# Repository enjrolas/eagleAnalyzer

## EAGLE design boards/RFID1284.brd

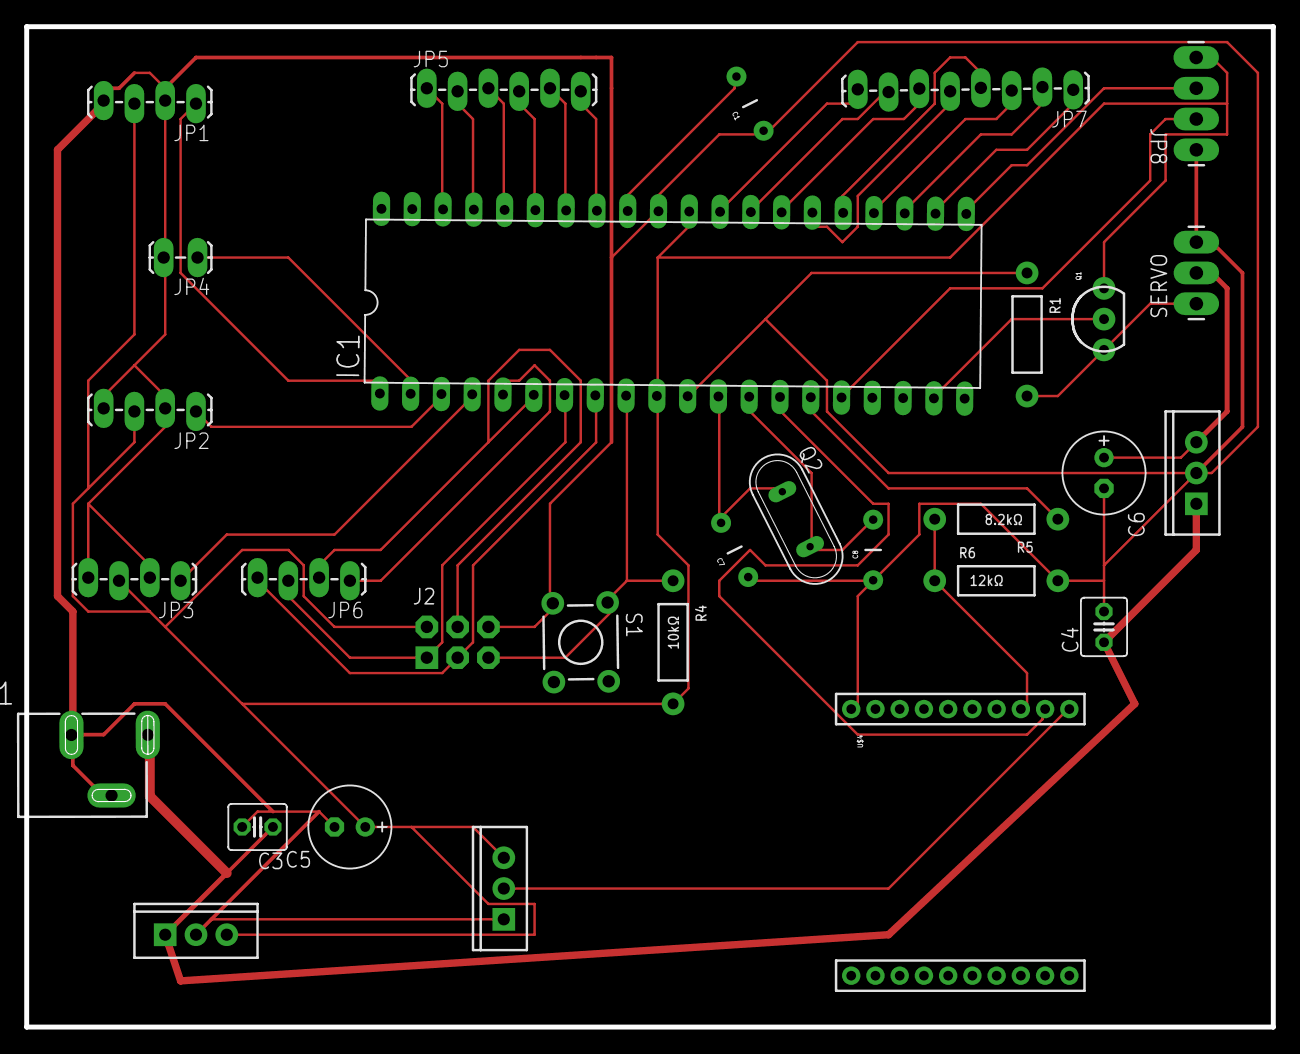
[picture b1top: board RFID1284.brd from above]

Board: 2 copper layers, 102.9 x 82.5 mm, 30 parts (0 on the bottom side), 38 nets.

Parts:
C1: 100nF; CAP-PTH-5MM
C3, C4: C025-040X050
C5, C6: E2,5-7
C7, C8: 20pF; CAP-PTH-5MM
IC1: DIL40
IC2, IC3, IC4: TO220-IGO
J1: POWER_JACKSLT; POWER_JACK_SLOT
J2: AVR_SPI_PRG_6NS; 2X3-NS
JP1, JP2, JP3, JP6: 1X04_LOCK_LONGPADS
JP4: 1X02_LOCK_LONGPADS
JP5: 1X06_LOCK_LONGPADS
JP7: 1X08_LOCK_LONGPADS
JP8: 1X04_LONGPADS
Q1: TO-92-AMMO
Q2: 16MHz; QS
R1: AXIAL-0.4
R4: 10kΩ; AXIAL-0.4
R5: 8.2kΩ; AXIAL-0.4
R6: 12kΩ; AXIAL-0.4
S1: TACTILE-PTH
SERVO: 1X03_LONGPADS
U$4: XBEE-1B1; XBEE-1

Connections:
5V: C5.+, IC1.10, IC1.30, IC2.OUT, IC4.OUT, J2.2, JP1.3, JP2.3, JP3.3, JP8.4, Q1.3, R4.P$2
DOOR_SWITCH: IC1.2, JP4.1
GND: C1.1, C3.2, C4.2, C5.-, C6.-, C7.1, C8.1, IC1.11, IC1.31, IC2.GND, IC3.GND, IC4.IN, J1.GND@1, J1.GND@2, J2.6, JP1.2, JP1.4, JP2.2, JP2.4, JP3.2, JP3.4, JP4.2, JP8.1, R1.P$1, R6.P$2, S1.3, SERVO.3, U$4.10
LOCK: IC1.3, JP2.1
LOCK_DELAY: IC1.4, JP3.1
MISO: IC1.7, J2.1, JP6.3
MOSI: IC1.6, J2.4, JP6.2
unnamed: C7.2, IC1.12, Q2.1
unnamed: C1.2, IC1.32
unnamed: C8.2, IC1.13, Q2.2
unnamed: IC1.38, JP5.1
unnamed: IC1.37, JP5.2
unnamed: IC1.36, JP5.3
unnamed: IC1.35, JP5.4
unnamed: IC1.34, JP5.5
unnamed: IC1.33, JP5.6
unnamed: IC1.22, JP7.1
unnamed: IC1.23, JP7.2
unnamed: IC1.24, JP7.3
unnamed: IC1.25, JP7.4
unnamed: IC1.26, JP7.5
unnamed: IC1.27, JP7.6
unnamed: IC1.28, JP7.7
unnamed: IC1.29, JP7.8
RESET: IC1.9, J2.5, R4.P$1, S1.1
RFID_ENABLE: IC1.21, JP8.3
RFID_SERIAL: IC1.16, JP8.2
SCK: IC1.8, J2.3, JP6.4
SERVO: IC1.19, Q1.2
SERVO_OUT: Q1.1, R1.P$2, SERVO.1
SERVO_VCC: C6.+, IC3.OUT, SERVO.2
SS: IC1.5, JP6.1
TX0: IC1.15, R5.P$1
TX0_LOW: R5.P$2, R6.P$1, U$4.3
UNLOCK: IC1.1, JP1.1
VCC: IC4.GND, U$4.1
VIN: C3.1, C4.1, IC2.IN, IC3.IN, J1.PWR
XBEE_OUT: IC1.14, U$4.2

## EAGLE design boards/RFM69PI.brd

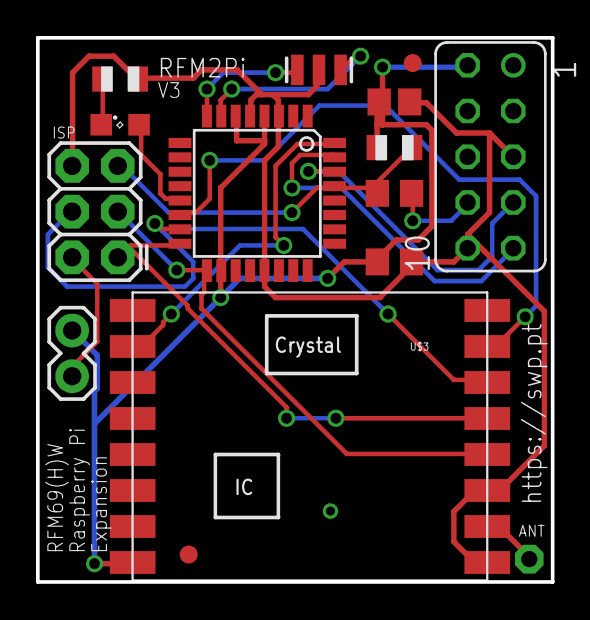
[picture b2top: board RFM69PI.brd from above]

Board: 2 copper layers, 28.6 x 30.2 mm, 15 parts (0 on the bottom side), 17 nets.

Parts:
ANT: 1,6/0,8
C4, C5, C7: 0.1uF; C0805
ISP: AVR_SPI_PRG_6PTH; 2X3
JP1: 1X02
LED1: SML0805
R1: 10K; R0805
RASPBERRY_PI: FE05-2
RLED: 220R; R0805
U2: ATMEGA168; TQFP32-08
U$1, U$2: FIDUCIAL; FIDUCIAL_1MM
U$3: RFM69; RFM69SMD
Y1: 16MHz; RESONATOR-SMD

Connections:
+3V3: C4.1, C7.1, JP1.2, R1.2, RASPBERRY_PI.2, U2.4, U2.6, U2.18, U$3.8
+5V: ISP.2, JP1.1
ANT: ANT.1, U$3.10
D0/RX: RASPBERRY_PI.7, U2.30
D1/TX: RASPBERRY_PI.9, U2.31
D2: U2.32, U$3.2
D9: LED1.A, U2.13
D10: U2.14, U$3.15
D11/MOSI: ISP.4, U2.15, U$3.14
D12/MISO: ISP.1, U2.16, U$3.13
D13/SCK: ISP.3, U2.17, U$3.12
GND: C4.2, C7.2, ISP.6, RASPBERRY_PI.5, RASPBERRY_PI.10, RLED.1, U2.3, U2.5, U2.21, U$3.9, U$3.11, Y1.2
unnamed: U2.7, Y1.1
unnamed: U2.8, Y1.3
unnamed: LED1.C, RLED.2
RESET: C5.2, ISP.5, R1.1, U2.29
_RESET: C5.1, RASPBERRY_PI.8

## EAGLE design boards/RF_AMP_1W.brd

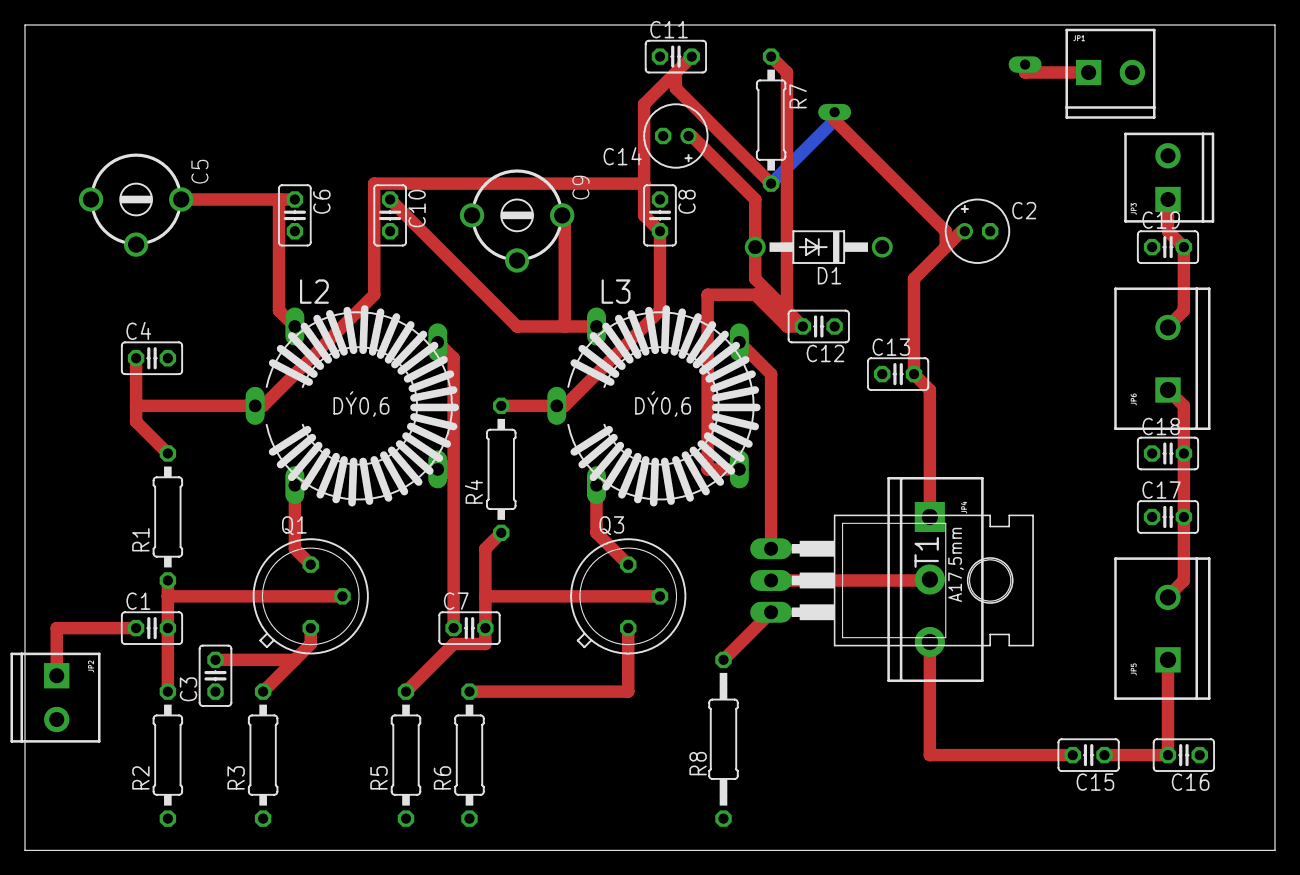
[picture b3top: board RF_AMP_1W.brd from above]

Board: 2 copper layers, 100.0 x 66.0 mm, 40 parts (1 on the bottom side), 21 nets.

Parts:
C1: C025-025X050
C2: 100uF; E2-5
C3, C7: 47nF; C025-025X050
C4, C8, C11, C12, C13, C15: 100nF; C025-025X050
C5, C9: CTRIM808-BC
C6, C10: 100pF; C025-025X050
C14: 10uF; E2-5
C16, C17, C18, C19: 560pF; C025-025X050
D1: 1N4004; DO41-10
JP1: SCREWTERMINAL-3.5MM-2
JP2: IN; SCREWTERMINAL-3.5MM-2
JP3: OUT; SCREWTERMINAL-3.5MM-2
JP4: SCREWTERMINAL-5MM-3
JP5: L7; SCREWTERMINAL-5MM-2
JP6: L8; SCREWTERMINAL-5MM-2
L1: JAF1 5uH VK200; 82114A
L2, L3: ED16
Q1, Q3: BFY50; TO39
R1, R4: 12K; 0207/10
R2, R5: 1.5K; 0207/10
R3: 100; 0207/10
R6: 33; 0207/10
R7: 1k; 0207/10
R8: 0207/12
T1: BUX85; TO220

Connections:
GND: C2.-, C3.1, C4.2, C5.2, C6.2, C8.1, C9.2, C10.2, C11.1, C12.1, C13.1, C14.-, C16.1, C17.1, C18.1, C19.1, D1.C, JP1.2, JP2.2, JP3.2, L2.OUT2, R2.1, R3.1, R5.1, R6.1, R8.1
unnamed: JP1.1, L1.1
unnamed: C2.+, C4.1, C8.2, C11.2, C13.2, JP4.1, L1.2, L2.A, L3.A, R1.2, R4.2, R7.2
unnamed: C1.2, Q1.2, R1.1, R2.2
unnamed: C1.1, JP2.1
unnamed: C3.2, Q1.1, R3.2
unnamed: L2.B, Q1.3
unnamed: C5.1, C6.1, L2.C
unnamed: R8.2, T1.3
unnamed: JP4.2, T1.2
unnamed: C7.2, Q3.2, R4.1, R5.2
unnamed: C15.2, JP4.3
unnamed: C15.1, C16.2, JP5.1
unnamed: Q3.1, R6.2
unnamed: L3.B, Q3.3
unnamed: C9.1, C10.1, L3.C
unnamed: L3.OUT1, T1.1
unnamed: C12.2, C14.+, D1.A, L3.OUT2, R7.1
unnamed: C7.1, L2.OUT1
unnamed: C17.2, C18.2, JP5.2, JP6.1
unnamed: C19.2, JP3.1, JP6.2

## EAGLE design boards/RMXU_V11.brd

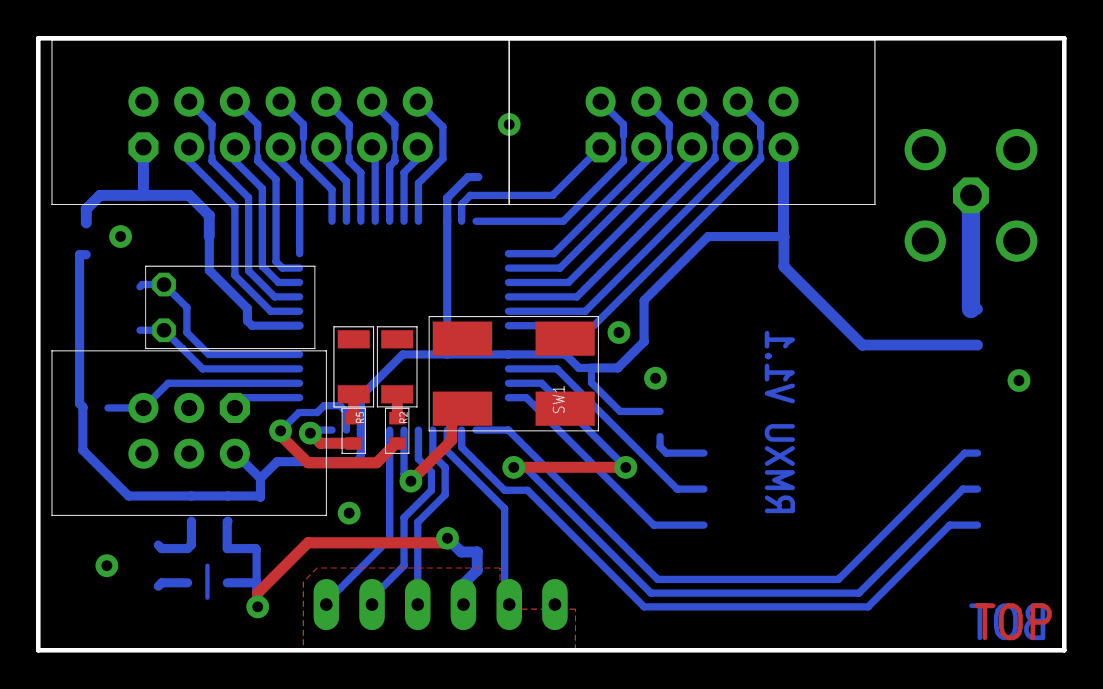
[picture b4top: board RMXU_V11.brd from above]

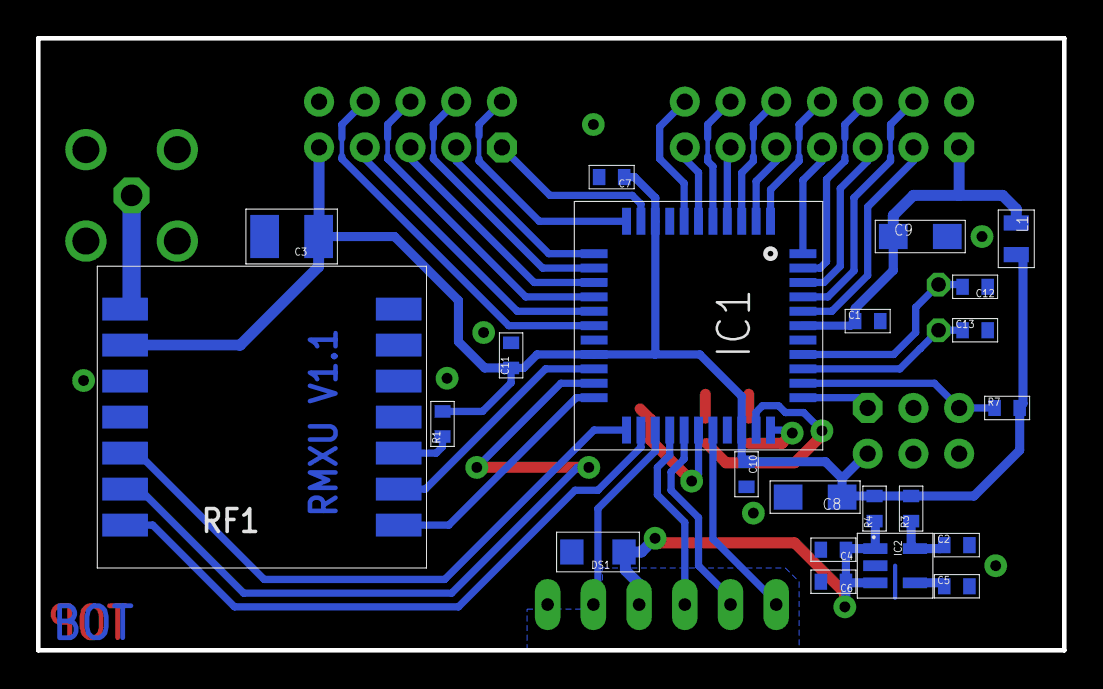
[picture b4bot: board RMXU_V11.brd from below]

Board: 2 copper layers, 57.0 x 34.0 mm, 42 parts (22 on the bottom side), 46 nets.

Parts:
C1, C6, C7, C10, C11: 100n; 0603
C2, C4: 1u; 0603
C3: 68u; SMC_B
C5: 10n; 0603
C8, C9: 10u; SMC_A
C12, C13: n.b.; 0603
DS1: SMF12A; SMF
IC1: XMEGA32A4U; TQFP44
IC2: LP2992IM5-3v3; SOT23-5
L1: 10uH; 0805
LED1: LEDG; 1206
LED3: LEDR; 1206
QR1: 32,768; TC26H
R1, R7: 10k; 0603
R2, R5: 1k; 0603
R3: 0R; 0603
R4: n.b.; 0603
RF1: RFM12B
SV1: PDI; ML6
SV2: PORTC; ML10
SV4: PORT A-B; ML14
SW1: SW1; SPNO
X2: ANT; T2.0/1.2
X3, X4, X5, X6: GND; T2.3/1.5
X7: DTR; T1.4/0.7L
X8: TX; T1.4/0.7L
X9: RX; T1.4/0.7L
X10: VCC; T1.4/0.7L
X11: CTS; T1.4/0.7L
X12: GND; T1.4/0.7L

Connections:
+3V3: C3.+, C7.1, C8.+, C10.1, C11.1, IC1.9, IC1.19, IC1.31, L1.2, R1.2, R3.2, R4.2, R7.2, RF1.VDD, SV1.2, SV2.9
CTS: IC1.25, X11.1
DTR: IC1.32, R2.2
GND: C1.2, C2.2, C3.-, C4.2, C5.2, C6.2, C7.2, C8.-, C9.-, C10.2, C11.2, C12.1, C13.2, DS1.A, IC1.8, IC1.18, IC1.30, IC1.38, IC2.2, LED1.2, LED3.2, RF1.GND, RF1.GND@1, SV1.6, SV2.10, SV4.2, SW1.1, SW1.2, X3.P$1, X4.P$1, X5.P$1, X6.P$1, X12.1
unnamed: IC1.10, SV2.1
unnamed: IC1.11, SV2.2
unnamed: IC1.12, SV2.3
unnamed: IC1.29, X7.1
unnamed: C12.2, IC1.37, QR1.1
unnamed: IC1.13, SV2.4
unnamed: IC1.14, SV2.5
unnamed: IC1.15, SV2.6
unnamed: IC1.16, SV2.7
unnamed: IC1.17, SV2.8
unnamed: RF1.ANT, X2.P$1
unnamed: IC1.33, R5.2
unnamed: C5.1, IC2.4
unnamed: IC1.28, SW1.3
unnamed: LED1.1, R2.1
unnamed: C13.1, IC1.36, QR1.2
unnamed: C2.1, IC2.5, R3.1
unnamed: R1.1, RF1.FFS
unnamed: LED3.1, R5.1
unnamed: C1.1, C9.+, IC1.39, L1.1, SV4.1
unnamed: IC1.7, SV4.14
unnamed: IC1.6, SV4.13
unnamed: IC1.5, SV4.12
unnamed: IC1.4, SV4.11
unnamed: IC1.3, SV4.10
unnamed: IC1.2, SV4.9
unnamed: IC1.1, SV4.8
unnamed: IC1.44, SV4.7
unnamed: IC1.43, SV4.6
unnamed: IC1.42, SV4.5
unnamed: IC1.41, SV4.4
unnamed: IC1.40, SV4.3
unnamed: IC1.34, SV1.1
unnamed: IC1.35, R7.1, SV1.5
RIRQ: IC1.20, RF1.IRQ
RSEL: IC1.24, RF1.SEL
RX: IC1.26, X9.1
RXDD0: IC1.22, RF1.SDO
TX: IC1.27, X8.1
TXDD0: IC1.23, RF1.SDI
VCC: C4.1, C6.1, DS1.C, IC2.1, IC2.3, R4.1, X10.1
XCKD0: IC1.21, RF1.SCK

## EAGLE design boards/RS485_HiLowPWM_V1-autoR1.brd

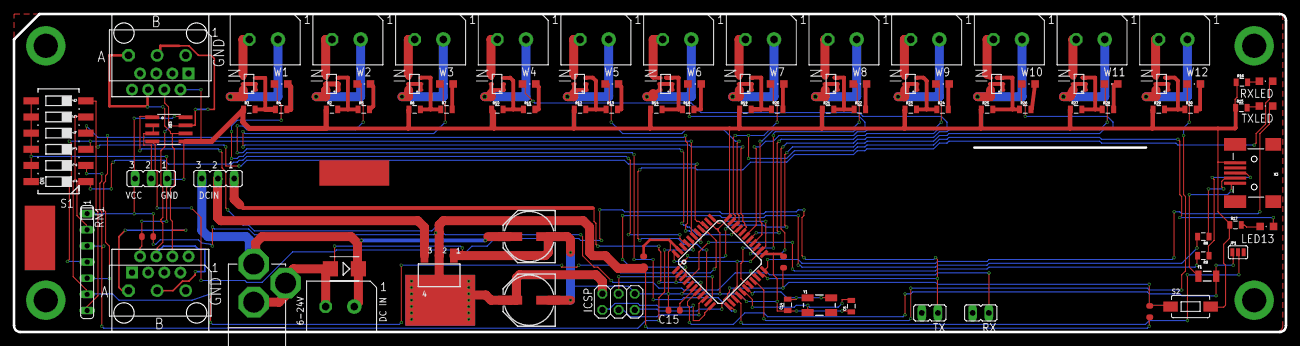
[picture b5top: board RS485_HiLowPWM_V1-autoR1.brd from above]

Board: 2 copper layers, 200.0 x 50.0 mm, 105 parts (0 on the bottom side), 94 nets.

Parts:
C3, C6, C7, C15: 100n; C0603-ROUND
C5, C14: 22p; 0805
C8: 47u; PANASONIC_E
C11: 100uF; PANASONIC_E
D1: M7; SMB
F1: PTCSMD; PTC-1206
IC1: ATMEGA32U4-AU; TQFP44
IC4: MC33269ST-5; SOT223
ICSP: ICSP; 2X03
JP1: PW_SW; SJ_3
JP3: PW_SOURCE; JP2
JP4: RS485_PW; JP2
JP10, JP11, JP12, JP13: M01-SMTSO-256-ET; SMTSO-256-ET
LED13: CHIPLED_0805
OUT1, OUT2: RJ45-8PTH; RJ45-8
R1: 10k; R0603-ROUND
R2, R3, R6, R10, R12, R14, R19, R21, R23, R25, R27, R29: 10K; 0805
R4, R5, R7, R11, R13, R18, R20, R22, R24, R26, R28, R30: 1K; 0805
R8, R9: 22; 0805
R15, R16, R17: 330; 0805
RN1: 1K; SIL7
RX: RX_TXO; JP1
RXLED: CHIPLED_0805
S1: 219-06; CTS-219-06
S2: RES; TACTILE-SWITCH-1101NE
TX: TX_RXI; JP1
TXLED: CHIPLED_0805
U$1, U$4, U$6, U$8, U$12, U$14, U$16, U$18, U$20, U$22, U$24, U$26: DECADE-NSS30201MR6T1G
U$2, U$5, U$7, U$9, U$11, U$13, U$15, U$17, U$19, U$21, U$23, U$25, U$27: DECADE-5MM-CONN; DECADE-5MM-CON-1X2
U$3: RS485SOIC; SO08
U$10: DECADE-LOGO-SMALL
U$28, U$29: DECADE-5MM-CON-1X3
U$30: LL-LUXURYLOGICO.COM; DECADE-LL-LOGO-SMALL
W1, W2, W3, W4, W5, W6, W7, W8, W9, W10, W11, W12: CHIPLED_0805
X1: DC21MMX; DC-21MM
X3: USBOLD; USB-MINIB-OLD
Y1: 16Mhz; CRYSTAL-SMD-5X3

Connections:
+5V: C6.1, C7.1, C8.+, IC4.2, IC4.4, ICSP.2, JP4.3, R1.2, RN1.1, U$3.8
A: OUT1.6, OUT2.6, U$3.6, U$28.3, U$29.3
B: OUT1.4, OUT2.4, U$3.7, U$28.2, U$29.2
D4: IC1.25, W11.A
D5: IC1.31, W5.A
D6: IC1.27, W4.A
D7: IC1.1, W10.A
D8: IC1.28, W9.A
D9: IC1.29, W3.A
D10: IC1.30, W2.A
D11: IC1.12, W1.A
D12: IC1.26, W8.A
D13: IC1.32, LED13.A, W7.A
GND: C3.2, C5.1, C6.2, C7.2, C8.-, C11.-, C14.1, C15.2, D1.A, IC1.5, IC1.15, IC1.23, IC1.33, IC1.35, IC1.43, IC4.1, ICSP.6, JP4.1, OUT1.2, OUT2.2, R2.1, R3.1, R6.1, R10.1, R12.1, R14.1, R15.1, R16.1, R17.1, R19.1, R21.1, R23.1, R25.1, R27.1, R29.1, S1.7, S1.8, S1.9, S1.10, S1.11, S1.12, S2.P$2, U$3.5, U$9.2, U$28.1, U$29.1, X1.1, X1.3, X3.GND
MISO: IC1.11, ICSP.1
MOSI: IC1.10, ICSP.4
unnamed: U$1.1, U$1.2, U$1.5, U$1.6, U$2.1
unnamed: R4.2, W1.C
unnamed: U$1.E, U$2.2
unnamed: R5.2, W2.C
unnamed: R3.2, R4.1, U$1.B
unnamed: C5.2, IC1.16, Y1.1
unnamed: C14.2, IC1.17, Y1.3
unnamed: R2.2, R5.1, U$4.B
unnamed: U$4.1, U$4.2, U$4.5, U$4.6, U$5.1
unnamed: U$4.E, U$5.2
unnamed: IC1.3, R8.2
unnamed: IC1.4, R9.2
unnamed: R8.1, X3.D-
unnamed: R9.1, X3.D+
unnamed: F1.1, X3.VBUS
unnamed: R15.2, TXLED.C
unnamed: R7.2, W3.C
unnamed: C15.1, IC1.6
unnamed: IC1.14, IC1.24, IC1.34, IC1.44, JP1.2
unnamed: R6.2, R7.1, U$6.B
unnamed: JP4.2, U$3.2, U$3.3
unnamed: U$6.1, U$6.2, U$6.5, U$6.6, U$7.1
unnamed: U$6.E, U$7.2
unnamed: R11.2, W4.C
unnamed: R10.2, R11.1, U$8.B
unnamed: U$8.1, U$8.2, U$8.5, U$8.6, U$11.1
unnamed: U$8.E, U$11.2
unnamed: R13.2, W5.C
unnamed: R12.2, R13.1, U$12.B
unnamed: U$12.1, U$12.2, U$12.5, U$12.6, U$13.1
unnamed: U$12.E, U$13.2
unnamed: R18.2, W6.C
unnamed: R14.2, R18.1, U$14.B
unnamed: U$14.1, U$14.2, U$14.5, U$14.6, U$15.1
unnamed: U$14.E, U$15.2
unnamed: R20.2, W7.C
unnamed: R16.2, RXLED.C
unnamed: LED13.C, R17.2
unnamed: R19.2, R20.1, U$16.B
unnamed: IC1.41, RN1.2, S1.1
unnamed: IC1.40, RN1.3, S1.2
unnamed: IC1.39, RN1.4, S1.3
unnamed: IC1.38, RN1.5, S1.4
unnamed: IC1.37, RN1.6, S1.5
unnamed: IC1.36, RN1.7, S1.6
unnamed: U$16.1, U$16.2, U$16.5, U$16.6, U$17.1
unnamed: U$16.E, U$17.2
unnamed: R22.2, W8.C
unnamed: R21.2, R22.1, U$18.B
unnamed: U$18.1, U$18.2, U$18.5, U$18.6, U$19.1
unnamed: U$18.E, U$19.2
unnamed: R24.2, W9.C
unnamed: R23.2, R24.1, U$20.B
unnamed: U$20.1, U$20.2, U$20.5, U$20.6, U$21.1
unnamed: U$20.E, U$21.2
unnamed: R26.2, W10.C
unnamed: R25.2, R26.1, U$22.B
unnamed: U$22.1, U$22.2, U$22.5, U$22.6, U$23.1
unnamed: U$22.E, U$23.2
unnamed: R28.2, W11.C
unnamed: R27.2, R28.1, U$24.B
unnamed: U$24.1, U$24.2, U$24.5, U$24.6, U$25.1
unnamed: U$24.E, U$25.2
unnamed: R30.2, W12.C
unnamed: R29.2, R30.1, U$26.B
unnamed: U$26.1, U$26.2, U$26.5, U$26.6, U$27.1
unnamed: U$26.E, U$27.2
RESET: C3.1, IC1.13, ICSP.5, R1.1, S2.P$1
RX: IC1.20, RX.1, U$3.1
SCK: IC1.9, ICSP.3
SCL: IC1.18, W6.A
SDA: IC1.19, W12.A
SS: IC1.8, RXLED.A
SUB_PW: IC4.3, JP3.2
TX: IC1.21, TX.1, U$3.4
TXA: IC1.22, TXLED.A
VBUS: F1.2, IC1.2, IC1.7, JP1.1, JP3.1
VIN: C11.+, D1.C, JP3.3, U$9.1, X1.2

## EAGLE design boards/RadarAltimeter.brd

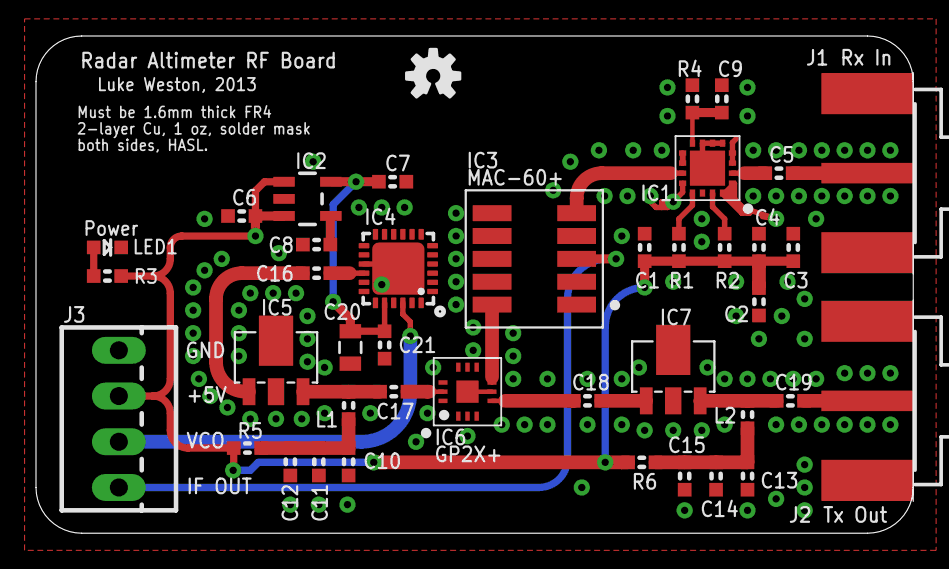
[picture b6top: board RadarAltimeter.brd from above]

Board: 2 copper layers, 48.7 x 27.6 mm, 41 parts (0 on the bottom side), 24 nets.

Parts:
C1, C4, C11, C14: 1nF; 0603
C2, C3: 100pF; 0603
C5, C16, C17, C18, C19: 68pF; 0603
C6, C7: 2.2µF; 0603
C8: 470pF; 0603
C9, C21: 10nF; 0603
C10, C13: 22pF; 0603
C12, C15: 1µF; 0603
C20: 4.7µF; 0805
IC1: HMC717LP3; 16-QFN
IC2: MIC5219; SOT23-5
IC3: MAC-60+; DZ1650
IC4: HMC431LP4; QFN24
IC5, IC7: GALI-84+; DF782
IC6: GP2X+; QFN12
J1: Rx; J502-ND-142-0701-881/886
J2: Tx; J502-ND-142-0701-881/886
J3: Interface; 22-23-2041
L1, L2: 22nH; 0603
LED1: Power; LED-0603
R1, R2, R5, R6: 0Ω; 0603
R3: 1kΩ; 0603
R4: 2.0kΩ; 0603
SY: OSHW-LOGOS; OSHW-LOGO-S

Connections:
+3.0V: C7.1, C20.1, C21.1, IC2.5, IC4.20
+5V: C1.2, C2.2, C3.2, C4.2, C6.1, IC2.1, IC2.3, J3.2, R1.2, R2.2, R3.2, R5.2, R6.2
GND: C1.1, C2.1, C3.1, C4.1, C6.2, C7.2, C8.1, C9.1, C10.1, C11.1, C12.1, C13.1, C14.1, C15.1, C20.2, C21.2, IC1.P$1, IC1.P$3, IC1.P$4, IC1.P$5, IC1.P$6, IC1.P$7, IC1.P$9, IC1.P$10, IC1.P$12, IC1.P$14, IC1.P$16, IC1.PAD, IC2.2, IC3.P$1, IC3.P$2, IC3.P$4, IC3.P$6, IC3.P$7, IC3.P$8, IC3.P$9, IC4.15, IC4.EXP, IC5.2, IC5.4, IC6.P$1, IC6.P$3, IC6.P$4, IC6.P$5, IC6.P$6, IC6.P$8, IC6.P$10, IC6.P$11, IC6.P$12, IC6.PAD, IC7.2, IC7.4, J1.G@1, J1.G@2, J1.G@3, J1.G@4, J2.G@1, J2.G@2, J2.G@3, J2.G@4, J3.1, LED1.C, R4.1
unnamed: C16.2, IC5.1
unnamed: C17.1, IC5.3, L1.2
unnamed: C10.2, C11.2, C12.2, L1.1, R5.1
unnamed: C16.1, IC4.16
unnamed: C17.2, IC6.P$2
unnamed: IC4.22, J3.3
unnamed: C18.2, IC7.1
unnamed: C19.1, IC7.3, L2.2
unnamed: C13.2, C14.2, C15.2, L2.1, R6.1
unnamed: C19.2, J2.1
unnamed: C18.1, IC6.P$9
unnamed: IC3.P$10, IC6.P$7
unnamed: C8.2, IC2.4
unnamed: IC3.P$3, J3.4
unnamed: C5.2, IC1.P$2
unnamed: C5.1, J1.1
unnamed: IC1.P$11, IC3.P$5
unnamed: C9.2, IC1.P$8, R4.2
unnamed: IC1.P$13, R1.1
unnamed: IC1.P$15, R2.1
unnamed: LED1.A, R3.1

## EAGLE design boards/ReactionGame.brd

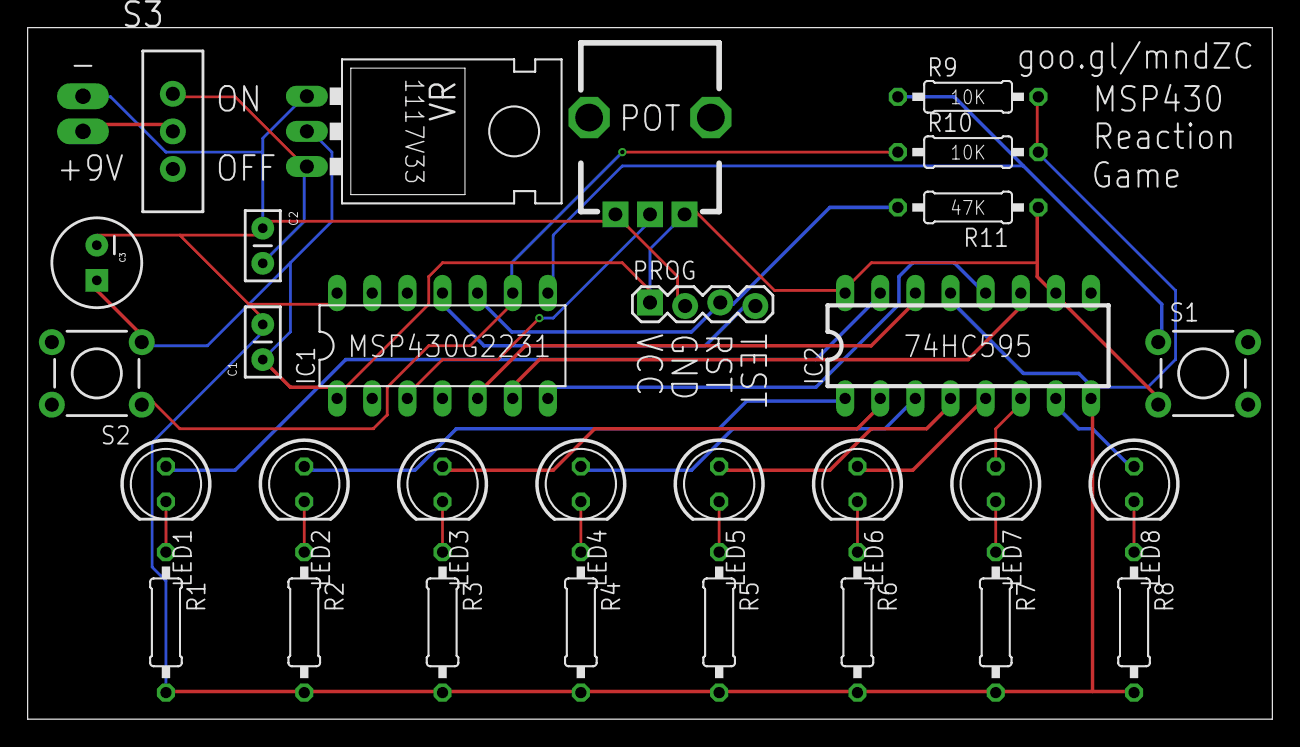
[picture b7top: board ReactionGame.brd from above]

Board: 2 copper layers, 90.0 x 50.0 mm, 31 parts (0 on the bottom side), 28 nets.

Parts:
9V_IN: 1X02_LONGPADS
C1, C2: 0.1uF; CAP-PTH-SMALL2
C3: 10uF; CPOL-RADIAL-100UF-25V
IC1: MSP430G2231; N14
IC2: 74HC595; DIL16
LED1, LED2, LED3, LED4, LED5, LED6, LED7, LED8: LED5MM
PROG: 1X04_LOCK
R1, R2, R3, R4, R5, R6, R7, R8: 150; 0207/10
R9, R10: 10k; 0207/10
R11: 47k; 0207/10
S1, S2: TACTILE-PTH
S3: SWITCH-SPDT_KIT
U$2: 10k; ALPS_POT
VR: LD1117V33; 78XXL

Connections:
unnamed: LED1.K, R1.1
unnamed: LED2.K, R2.1
unnamed: LED3.K, R3.1
unnamed: LED4.K, R4.1
unnamed: LED5.K, R5.1
unnamed: LED6.K, R6.1
unnamed: LED7.K, R7.1
unnamed: LED8.K, R8.1
unnamed: IC2.15, LED1.A
unnamed: IC2.1, LED2.A
unnamed: IC2.2, LED3.A
unnamed: IC2.3, LED4.A
unnamed: IC2.4, LED5.A
unnamed: IC2.5, LED6.A
unnamed: IC2.6, LED7.A
unnamed: IC2.7, LED8.A
unnamed: IC1.3, U$2.P$2
unnamed: IC1.10, PROG.3, R11.2
unnamed: IC1.5, IC2.14
unnamed: IC1.7, IC2.12
unnamed: IC1.6, IC2.11
unnamed: IC1.8, R9.1, S1.1
unnamed: IC1.9, R10.1, S2.1
unnamed: 9V_IN.2, C1.2, C2.1, C3.2, IC1.14, IC2.8, IC2.13, PROG.2, R1.2, R2.2, R3.2, R4.2, R5.2, R6.2, R7.2, R8.2, R9.2, R10.2, U$2.P$1, VR.IN
unnamed: IC1.11, PROG.4
unnamed: 9V_IN.1, S3.2
unnamed: C2.2, S3.1, VR.OUT
unnamed: C1.1, C3.1, IC1.1, IC2.10, IC2.16, PROG.1, R11.1, S1.3, S2.3, U$2.P$3, VR.GND

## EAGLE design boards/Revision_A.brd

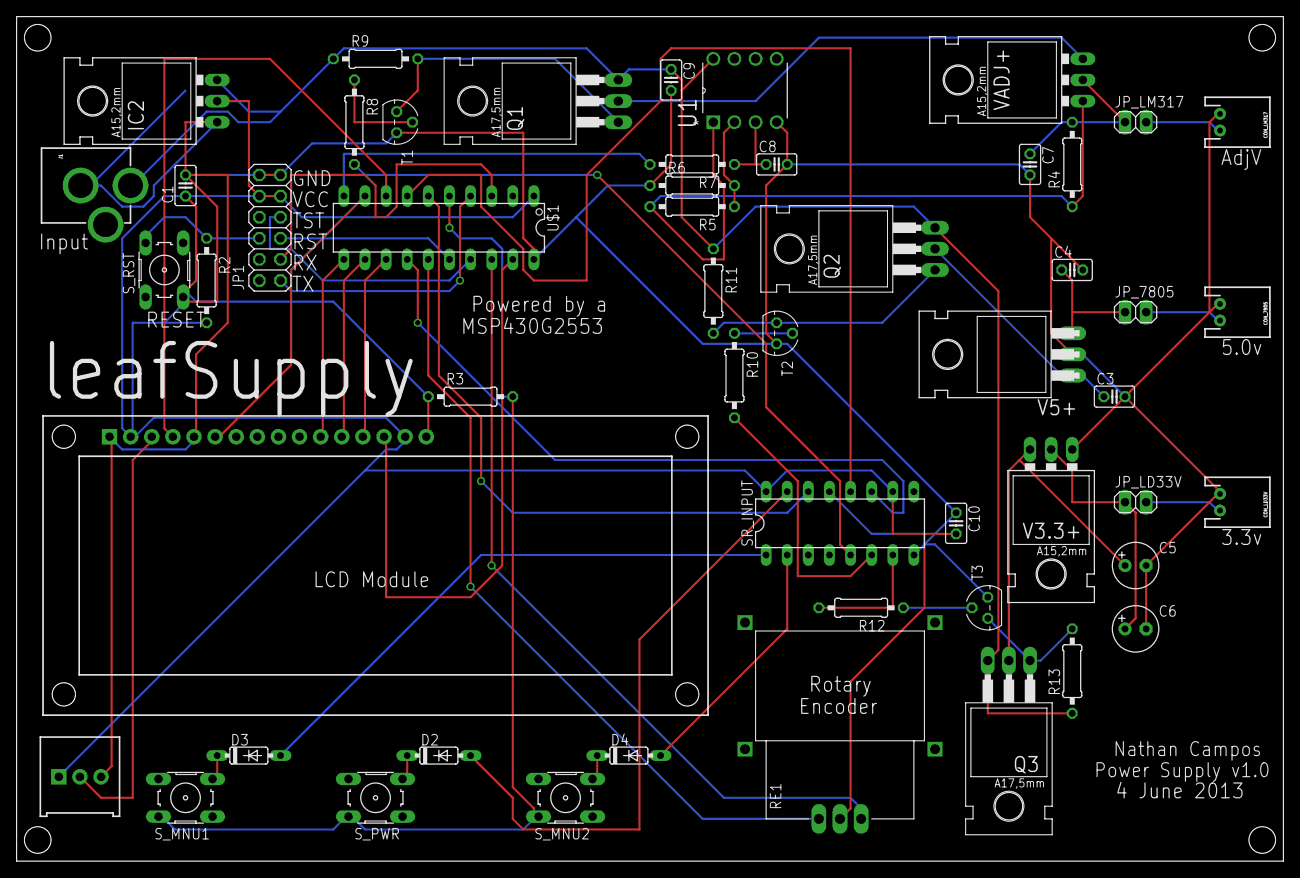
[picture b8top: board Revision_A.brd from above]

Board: 2 copper layers, 152.4 x 101.6 mm, 52 parts (0 on the bottom side), 49 nets.

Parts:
C1, C4, C7, C8, C9, C10: 0.1uF; C025-025X050
C3: 0.47uF; C025-025X050
C5, C6: 10uF; E2,5-6
CON_7805: M02JST-PTH-2; JST-2-PTH
CON_LD33V: M02JST-PTH-2; JST-2-PTH
CON_LM317: M02JST-PTH-2; JST-2-PTH
D2, D3, D4: 1N4148DO35-7; DO35-7
IC2: LD117AV33; TO220L1
J1: POWER_JACKPTH; POWER_JACK_PTH
JP1: 2X06
JP_7805: 1X02
JP_LD33V: 1X02
JP_LM317: 1X02
Q1, Q2, Q3: IRF9530; TO220
R1: TRIMPOT-PTH-KNOB; 3386U
R2, R3, R8, R9, R10, R11, R12, R13: 10kΩ; 0207/10
R4: 240Ω; 0207/10
R5, R6, R7: 100kΩ; 0207/10
RE1: ECW1J-B24-BCCO24LECW1J-B; ECW1J-B
SR_INPUT: 74HC595N; DIL16
S_MNU1, S_MNU2: B3F-10XX
S_PWR: B3F-10XX
S_RST: B3F-10XX
T1, T2, T3: BC547; TO92
U1: TLV2372IP; DIP254P762X508-8
U2: LCD-16X2SILK; LCD-16X2
U$1: G2XX3---N20; N20
V3.3+: LD117AV33; TO220L1
V5+: 7805T; TO220H
VADJ+: 317TL

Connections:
7805_IN: C3.1, Q2.2, V5+.1
7805_OUT: C4.1, JP_7805.1, V5+.3
+5V: C1.1, C10.2, IC2.2, JP1.9, JP1.10, R1.1, R2.2, RE1.PC, SR_INPUT.10, SR_INPUT.16, U2.2, U2.15, U$1.1
CLOCK: SR_INPUT.11, U$1.14
D4: U2.11, U$1.11
D5: U2.12, U$1.12
D6: U2.13, U$1.13
D7: U2.14, U$1.19
DATA: SR_INPUT.14, U$1.6
ENABLE: U2.6, U$1.9
GND: C1.2, C3.2, C4.2, C5.-, C6.-, C7.2, C8.2, C9.2, C10.1, CON_7805.1, CON_LD33V.1, CON_LM317.1, IC2.1, J1.GND, JP1.11, JP1.12, R1.3, R3.1, R6.1, SR_INPUT.8, SR_INPUT.13, S_RST.3, T1.1, T2.1, T3.1, U1.4, U2.1, U2.5, U2.16, U$1.20, V3.3+.1, V5+.2
INT: R3.2, S_MNU1.2, S_MNU2.2, S_PWR.2, U$1.5
LATCH: SR_INPUT.12, U$1.7
LD33V_IN: C5.+, Q3.2, V3.3+.3
LD33V_OUT: C6.+, JP_LD33V.1, V3.3+.2
LM317_ADJ: R4.1, R5.2, U1.1, VADJ+.1
LM317_IN: Q1.2, VADJ+.3
LM317_OUT: C7.1, JP_LM317.1, R4.2, VADJ+.2
unnamed: R1.2, U2.3
unnamed: D2.C, S_PWR.3
unnamed: JP1.6, R2.1, S_RST.2
unnamed: D3.C, S_MNU1.3
unnamed: D4.C, S_MNU2.3
unnamed: R5.1, R6.2, U1.2
unnamed: C8.1, R7.1, U1.3
unnamed: R8.1, T1.2
unnamed: Q1.1, R9.2, T1.3
unnamed: R10.1, T2.2
unnamed: D3.A, SR_INPUT.1
unnamed: Q2.1, R11.2, T2.3
unnamed: R12.1, T3.2
unnamed: Q3.1, R13.2, T3.3
unnamed: CON_LM317.2, JP_LM317.2
unnamed: D4.A, SR_INPUT.2
unnamed: D2.A, SR_INPUT.15
unnamed: CON_7805.2, JP_7805.2
unnamed: CON_LD33V.2, JP_LD33V.2
PWM: R7.2, U$1.10
RE_A: RE1.PA, U$1.15
RE_B: RE1.PB, U$1.18
RS: U2.4, U$1.8
RST: JP1.5, U$1.16
RX: JP1.3, U$1.3
TEST: JP1.7, U$1.17
TX: JP1.1, U$1.4
T_3V3: R12.2, SR_INPUT.7
T_5V: R10.2, SR_INPUT.6
T_ADJV: R8.2, SR_INPUT.5
VIN: C9.1, IC2.3, J1.PWR, Q1.3, Q2.3, Q3.3, R9.1, R11.1, R13.1, U1.8

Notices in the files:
parts and their libraries:
SparkFun: Licensing: CC v3.0 Share-Alike You are welcome to use this library for commercial purposes.
